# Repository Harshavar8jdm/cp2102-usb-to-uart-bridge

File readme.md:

# CP2102N USB-C to UART Bridge Module

## Description
A 32x16mm, two-layer USB-to-UART bridge converter based on the Silicon Labs CP2102N. This board provides a serial interface for hardware development and debugging.

The design includes specific additions to address reliability issues common in similar modules, specifically the addition of TVS diodes for ESD protection and proper CC pin termination for USB-C standard compliance.

## Specifications
*   **Controller:** Silicon Labs CP2102N
*   **Connector:** USB Type-C
*   **Logic Level:** 3.3V (with 5V VBUS passthrough)
*   **Dimensions:** 32mm x 16mm
*   **PCB Layers:** 2
*   **EDA Tool:** KiCad

## Hardware Features
*   **ESD Protection:** uClamp3601P TVS diodes on the VBUS, D+, and D- lines, placed at the connector to clamp transient voltages.
*   **USB-C Termination:** Independent 5.1k Ohm pull-down resistors (R1, R2) on the CC1 and CC2 pins for host detection with C-to-C cables.
*   **Layout:** Continuous bottom ground plane for return paths. Decoupling capacitors (C1-C4) are routed near the IC power pins.
*   **Pinout:** 3V3, GND, TXD, RXD, and 5V broken out to a standard 2.54mm pitch header.

## Board Images

### Schematic

### PCB Layout (Revised)

### 3D Render (Top)

### 3D Render (Bottom)

## Assembly Notes
The CP2102N utilizes a QFN-28 package with an exposed center pad. Solder paste and a reflow profile or hot plate are required for correct termination of the ground pad. The TVS diodes and passives are standard surface mount components.

## Author
Harsha

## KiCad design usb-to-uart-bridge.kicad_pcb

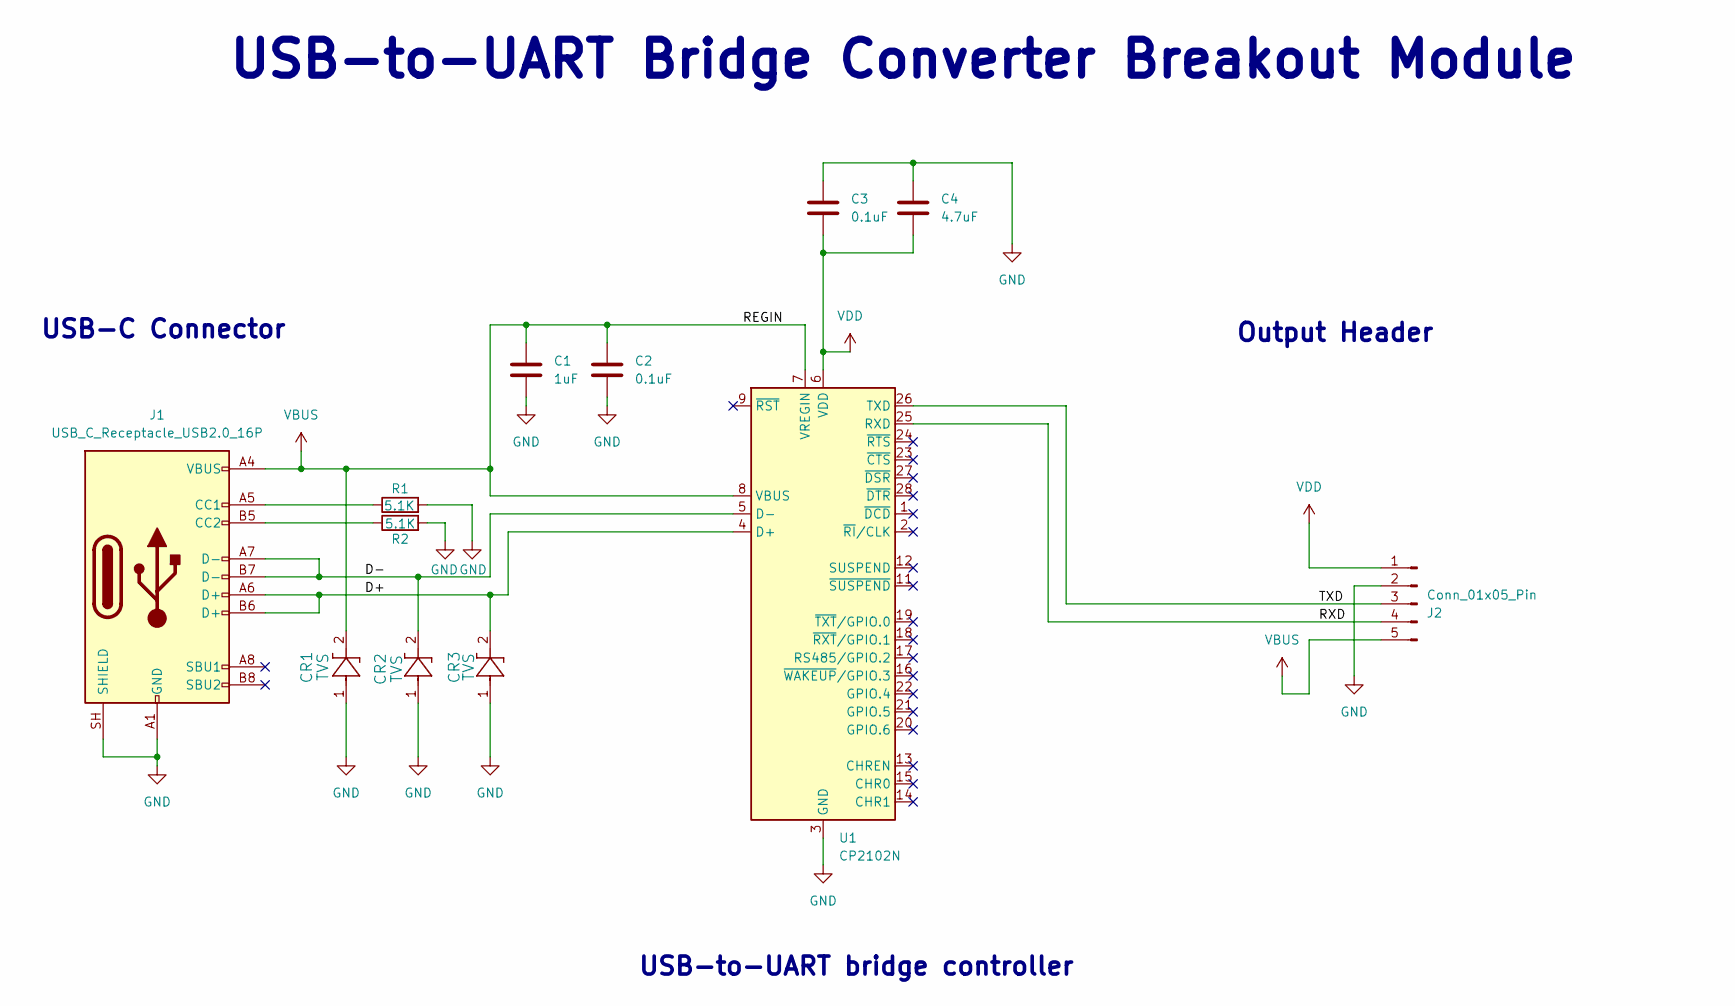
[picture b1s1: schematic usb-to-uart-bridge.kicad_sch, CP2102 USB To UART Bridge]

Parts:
C1: 1uF; C_0402_1005Metric
C2, C3: 0.1uF; C_0402_1005Metric
C4: 4.7uF; C_0402_1005Metric
CR1, CR2, CR3: TVS; SLP1006P2_SEM
J1: USB_C_Receptacle_USB2.0_16P; USB_C_Receptacle_HRO_TYPE-C-31-M-12
J2: Conn_01x05_Pin; PinHeader_1x05_P2.54mm_Horizontal
R1, R2: 5.1K; R_0402_1005Metric_Pad0.72x0.64mm_HandSolder
U1: CP2102N; QFN-28-1EP_5x5mm_P0.5mm_EP3.35x3.35mm

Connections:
/D+: CR3.2, J1.A6 (D+), J1.B6 (D+), U1.4 (D+)
/D-: CR2.2, J1.A7 (D-), J1.B7 (D-), U1.5 (D-)
/RXD: J2.4, U1.25 (RXD)
/TXD: J2.3, U1.26 (TXD)
GND: C1.2, C2.2, C3.1, C4.1, CR1.1, CR2.1, CR3.1, J1.A1 (GND), J1.A12 (GND), J1.B1 (GND), J1.B12 (GND), J1.SH (SHIELD), J2.2, R1.2, R2.2, U1.3 (GND), U1.29 (GND)
unnamed: J1.A5 (CC1), R1.1
unnamed: J1.B5 (CC2), R2.1
VBUS: C1.1, C2.1, CR1.2, J1.A4 (VBUS), J1.A9 (VBUS), J1.B4 (VBUS), J1.B9 (VBUS), J2.5, U1.7 (VREGIN), U1.8 (VBUS)
VDD: C3.2, C4.2, J2.1, U1.6 (VDD)

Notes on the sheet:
USB-C Connector
Output Header
USB-to-UART Bridge Converter Breakout Module
USB-to-UART bridge controller

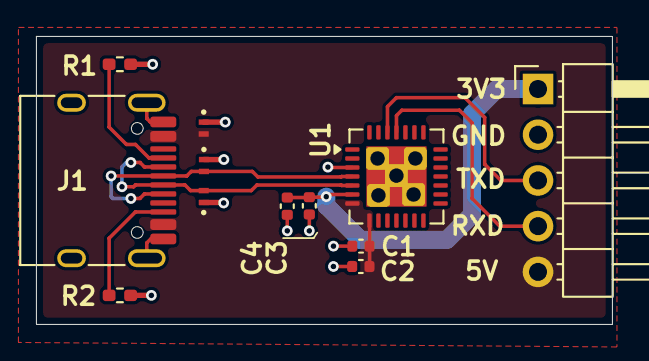
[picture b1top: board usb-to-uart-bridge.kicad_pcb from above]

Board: 2 copper layers, 32.0 x 16.0 mm, 12 parts (0 on the bottom side), 9 nets.
